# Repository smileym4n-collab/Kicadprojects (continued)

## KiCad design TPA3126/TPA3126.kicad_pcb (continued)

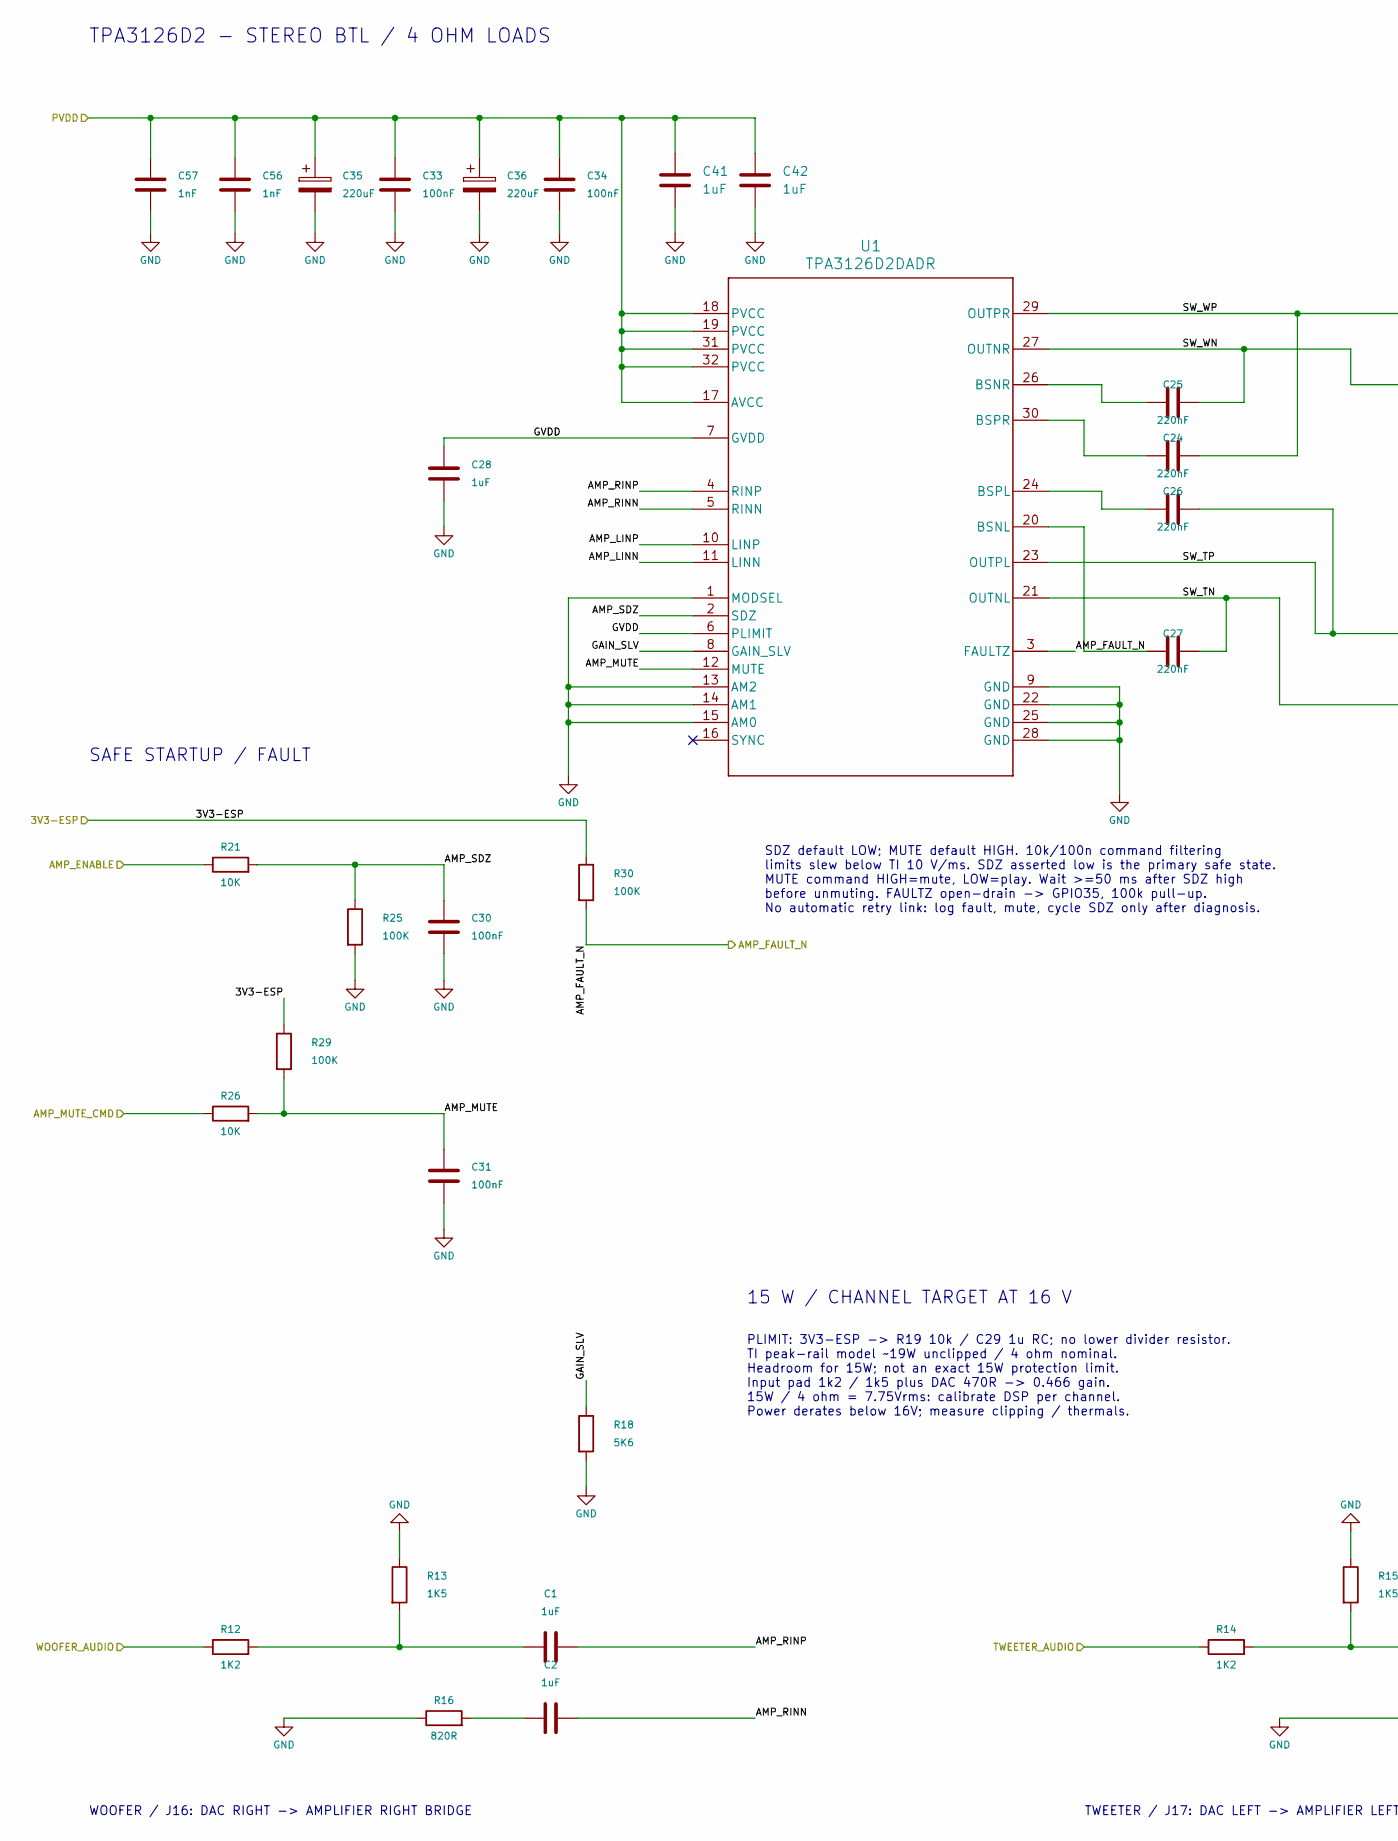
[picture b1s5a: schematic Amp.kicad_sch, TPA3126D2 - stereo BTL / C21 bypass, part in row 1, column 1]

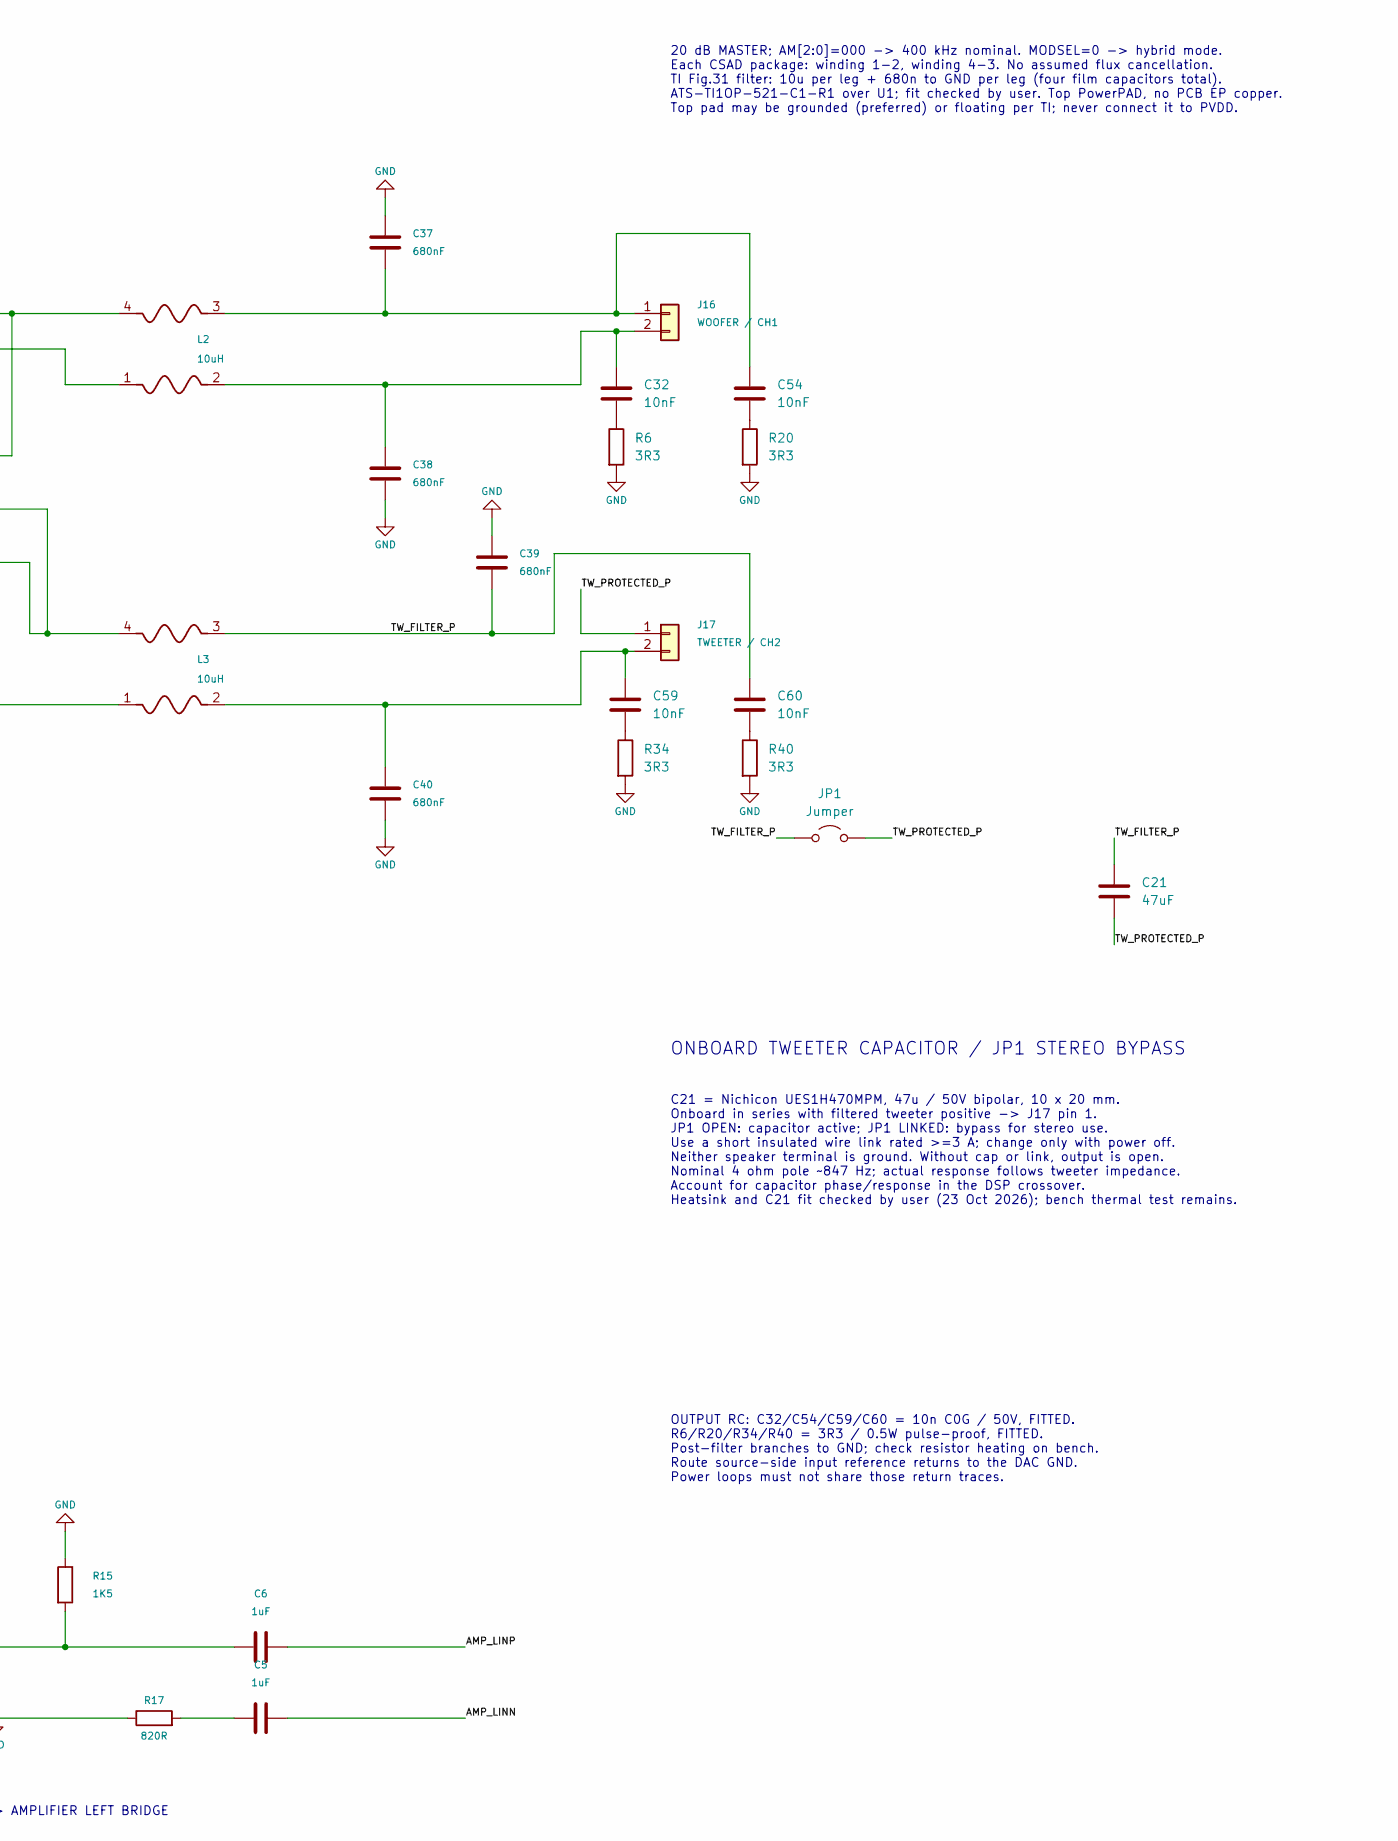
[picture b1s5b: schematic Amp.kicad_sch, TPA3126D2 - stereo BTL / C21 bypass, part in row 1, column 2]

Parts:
C1, C2, C5, C6: 1uF; C_Rect_L7.2mm_W5.0mm_P5.00mm; Voltage_Rating 63 V; Tolerance 5%; MPN R82DC4100AA60J
C21: 47uF; C_Radial_D10.0mm_H20.0mm_P5.00mm; Voltage_Rating 50 V; Tolerance 20%; MPN UES1H470MPM
C24, C25, C26, C27: 220nF; C_0805_2012Metric_Pad1.18x1.45mm_HandSolder; MPN CL21B224KAFNNNE
C28: 1uF; C_0805_2012Metric_Pad1.18x1.45mm_HandSolder; Voltage_Rating 25 V; Tolerance 10%; MPN C0805C105K3RACTU
C30, C31, C33, C34: 100nF; C_0603_1608Metric_Pad1.08x0.95mm_HandSolder; Voltage_Rating 50 V; Tolerance 10%; MPN MC0603B104K500CT
C32, C54, C59, C60: 10nF; C_0805_2012Metric_Pad1.18x1.45mm_HandSolder; Voltage_Rating 50 V; Tolerance 1%; MPN MC0805N103F500CT
C35, C36: 220uF; CP_Radial_D8.0mm_P3.50mm; MPN 35ZLH220MEFC8X11.5
C37, C38, C39, C40: 680nF; C_Rect_L18.0mm_W7.0mm_P15.00mm_FKS3_FKP3; MPN ECW-FE2W684J
C41, C42: 1uF; C_1206_3216Metric_Pad1.33x1.80mm_HandSolder; Manufacturer_Part_Number MCMHR50V105M4X7
C56, C57: 1nF; C_0603_1608Metric_Pad1.08x0.95mm_HandSolder; Voltage_Rating 50 V; Tolerance 10%; MPN CL10B102KB8NNNC
J16: WOOFER / CH1; Molex_KK-396_5273-02A_1x02_P3.96mm_Vertical; MPN 09-65-2028
J17: TWEETER / CH2; Molex_KK-396_5273-02A_1x02_P3.96mm_Vertical; MPN 09-65-2028
JP1: Jumper; TestPoint_2Pads_Pitch5.08mm_Drill1.3mm
L2, L3: 10uH; CSAD0660-100M; MPN CSAD0660-100M
R6, R20, R34, R40: 3R3; R_0805_2012Metric_Pad1.20x1.40mm_HandSolder; Tolerance 1%; MPN CRCW08053R30FKEAHP
R12, R14: 1K2; R_0805_2012Metric_Pad1.20x1.40mm_HandSolder; MPN RMCF0805FT1K20
R13, R15: 1K5; R_0805_2012Metric_Pad1.20x1.40mm_HandSolder; MPN RMCF0805FT1K50
R16, R17: 820R; R_0805_2012Metric_Pad1.20x1.40mm_HandSolder; Manufacturer_Part_Number RR1220P-821-D
R18: 5K6; R_0805_2012Metric_Pad1.20x1.40mm_HandSolder; MPN RMCF0805FT5K60
R21, R26: 10K; R_0805_2012Metric_Pad1.20x1.40mm_HandSolder; MPN RK73B2ATTD103J
R25, R29, R30: 100K; R_0805_2012Metric_Pad1.20x1.40mm_HandSolder; Manufacturer_Part_Number RK73B2ATTE104J
U1: TPA3126D2DADR; Texas_DAD0032A_HTSSOP-32_6.1x11mm_P0.65mm_TopEP3.71x3.81mm; MPN TPA3126D2DADR

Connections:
/3V3-ESP: R29.1, R30.1; also elsewhere on the board
/AMP/AMP_ENABLE: R21.1; also elsewhere on the board
/AMP/AMP_FAULT_N: R30.2, U1.3 (FAULTZ); also elsewhere on the board
/AMP/AMP_LINN: C5.2, U1.11 (LINN)
/AMP/AMP_LINP: C6.2, U1.10 (LINP)
/AMP/AMP_MUTE: C31.1, R26.2, R29.2, U1.12 (MUTE)
/AMP/AMP_MUTE_CMD: R26.1; also elsewhere on the board
/AMP/AMP_RINN: C2.2, U1.5 (RINN)
/AMP/AMP_RINP: C1.2, U1.4 (RINP)
/AMP/AMP_SDZ: C30.1, R21.2, R25.1, U1.2 (SDZ)
/AMP/GAIN_SLV: R18.1, U1.8 (GAIN_SLV)
/AMP/GVDD: C28.1, U1.6 (PLIMIT), U1.7 (GVDD)
/AMP/SW_TN: C27.2, L3.1, U1.21 (OUTNL)
/AMP/SW_TP: C26.2, L3.4, U1.23 (OUTPL)
/AMP/SW_WN: C25.2, L2.1, U1.27 (OUTNR)
/AMP/SW_WP: C24.2, L2.4, U1.29 (OUTPR)
/AMP/TWEETER_AUDIO: R14.1; also elsewhere on the board
/AMP/TW_FILTER_P: C21.1, C39.2, C60.1, JP1.1 (A), L3.3
/AMP/TW_PROTECTED_P: C21.2, J17.1, JP1.2 (B)
/AMP/WOOFER_AUDIO: R12.1; also elsewhere on the board
/PVDD: C33.1, C34.1, C35.1, C36.1, C41.1, C42.1, C56.1, C57.1, U1.17 (AVCC), U1.18 (PVCC), U1.19 (PVCC), U1.31 (PVCC), U1.32 (PVCC); also elsewhere on the board
GND: C28.2, C30.2, C31.2, C33.2, C34.2, C35.2, C36.2, C37.1, C38.2, C39.1, C40.2, C41.2, C42.2, C56.2, C57.2, R6.2, R13.1, R15.1, R16.1, R17.1, R18.2, R20.2, R25.2, R34.2, R40.2, U1.1 (MODSEL), U1.9 (GND), U1.13 (AM2), U1.14 (AM1), U1.15 (AM0), U1.22 (GND), U1.25 (GND), U1.28 (GND); also elsewhere on the board
unnamed: C1.1, R12.2, R13.2
unnamed: C2.1, R16.2
unnamed: C5.1, R17.2
unnamed: C6.1, R14.2, R15.2
unnamed: C32.2, R6.1
unnamed: C54.2, R20.1
unnamed: C59.2, R34.1
unnamed: C60.2, R40.1
unnamed: C37.2, C54.1, J16.1, L2.3
unnamed: C32.1, C38.1, J16.2, L2.2
unnamed: C40.1, C59.1, J17.2, L3.2
unnamed: C27.1, U1.20 (BSNL)
unnamed: C25.1, U1.26 (BSNR)
unnamed: C26.1, U1.24 (BSPL)
unnamed: C24.1, U1.30 (BSPR)

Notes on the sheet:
C21 = Nichicon UES1H470MPM, 47u / 50V bipolar, 10 x 20 mm. Onboard in series with filtered tweeter positive -> J17 pin 1. JP1 OPEN: capacitor active; JP1 LINKED: bypass for stereo use. Use a short insulated wire link rated >=3 A; change only with power off. Neither speaker terminal is ground. Witho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
ONBOARD TWEETER CAPACITOR / JP1 STEREO BYPASS
SAFE STARTUP / FAULT
WOOFER / J16: DAC RIGHT -> AMPLIFIER RIGHT BRIDGE
OUTPUT RC: C32/C54/C59/C60 = 10n C0G / 50V, FITTED. R6/R20/R34/R40 = 3R3 / 0.5W pulse-proof, FITTED. Post-filter branches to GND; check resistor heating on bench. Route source-side input reference returns to the DAC GND. Power loops must not share those return traces.
SDZ default LOW; MUTE default HIGH. 10k/100n command filtering limits slew below TI 10 V/ms. SDZ asserted low is the primary safe state. MUTE command HIGH=mute, LOW=play. Wait >=50 ms after SDZ high before unmuting. FAULTZ open-drain -> GPIO35, 100k pull-up. No automatic retry link: log fault, mute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
TPA3126D2 - STEREO BTL / 4 OHM LOADS
15 W / CHANNEL TARGET AT 16 V
TWEETER / J17: DAC LEFT -> AMPLIFIER LEFT BRIDGE
20 dB MASTER; AM[2:0]=000 -> 400 kHz nominal. MODSEL=0 -> hybrid mode. Each CSAD package: winding 1-2, winding 4-3. No assumed flux cancellation. TI Fig.31 filter: 10u per leg + 680n to GND per leg (four film capacitors total). ATS-TI1OP-521-C1-R1 over U1; fit checked by user. Top PowerPAD, no PCB 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
PLIMIT: 3V3-ESP -> R19 10k / C29 1u RC; no lower divider resistor. TI peak-rail model ~19W unclipped / 4 ohm nominal. Headroom for 15W; not an exact 15W protection limit. Input pad 1k2 / 1k5 plus DAC 470R -> 0.466 gain. 15W / 4 ohm = 7.75Vrms: calibrate DSP per channel. Power derates below 16V; mea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

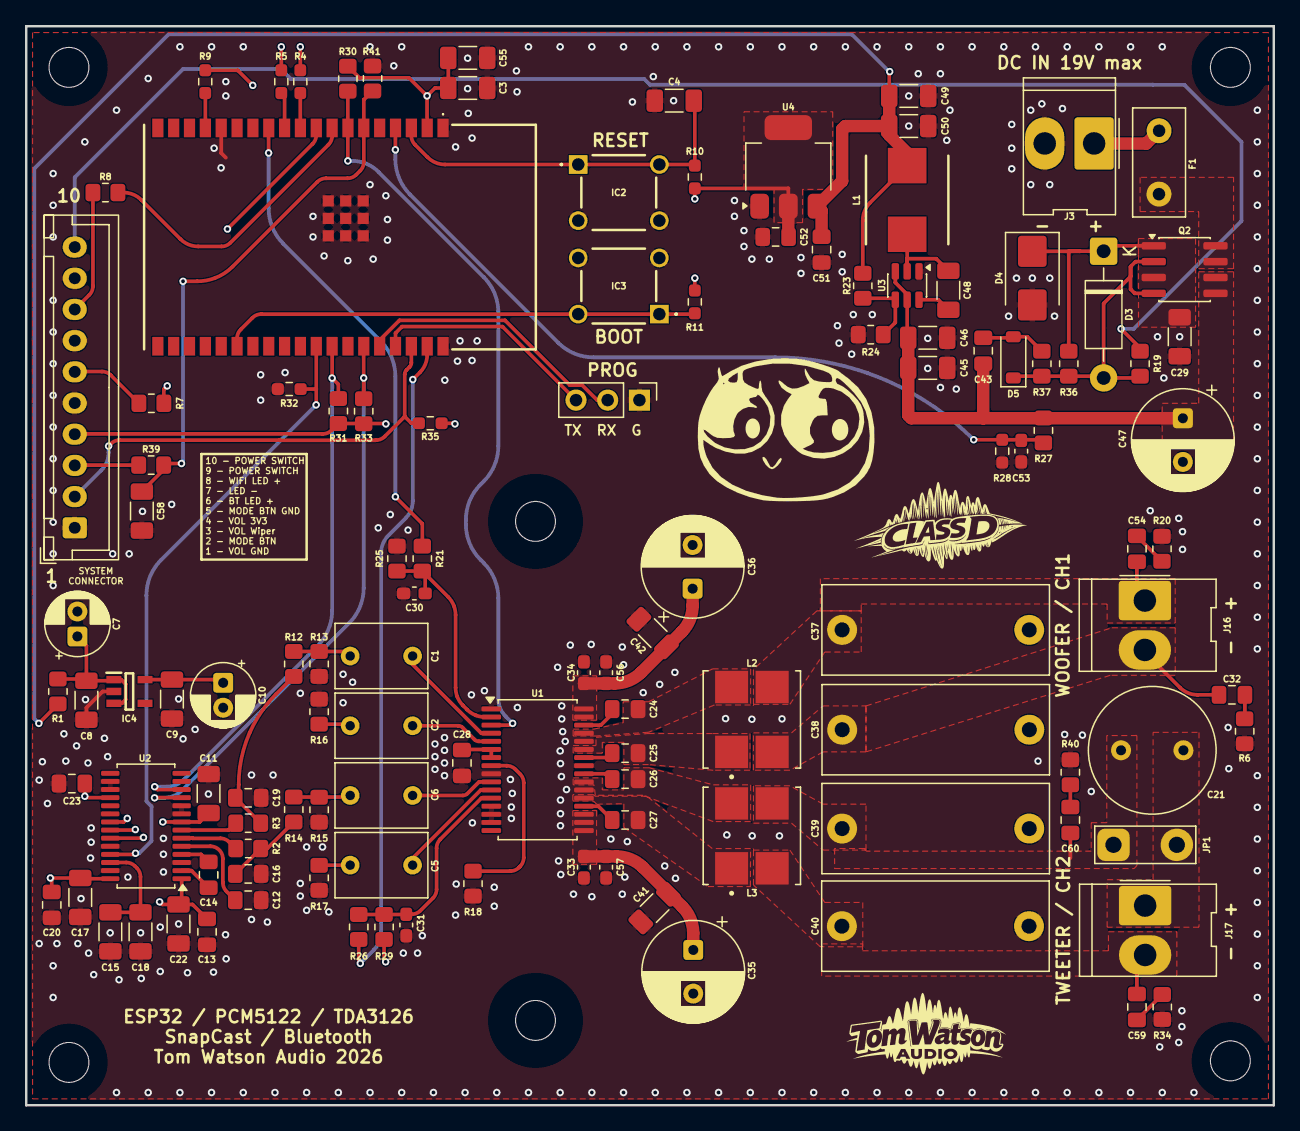
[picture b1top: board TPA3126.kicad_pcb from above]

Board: 4 copper layers, 100.0 x 86.5 mm, 125 parts (0 on the bottom side), 76 nets.

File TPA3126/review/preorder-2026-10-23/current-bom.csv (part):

Reference,Value,Footprint,Recorded MPN,Inventory ID,Saved assembly note,Review status
H1,MountingHole,MountingHole:MountingHole_3.2mm_M3,,,,Saved fields only; not a purchase approval
H2,MountingHole,MountingHole:MountingHole_3.2mm_M3,,,,Saved fields only; not a purchase approval
H3,MountingHole,MountingHole:MountingHole_3.2mm_M3,,,,Saved fields only; not a purchase approval
H4,MountingHole,MountingHole:MountingHole_3.2mm_M3,,,,Saved fields only; not a purchase approval
HS1,Heatsink,Custom:Heatsink_ATS_ATS-TI1OP-521-C1-R1_50x13.9mm_H25mm_P40mm,,,,Saved fields only; not a purchase approval
C3,100nF,Capacitor_SMD:C_1206_3216Metric_Pad1.33x1.80mm_HandSolder,C1206C104K5RACTU,157,,Saved fields only; not a purchase approval
C4,1uF,Capacitor_SMD:C_1206_3216Metric_Pad1.33x1.80mm_HandSolder,CL31B105KBHNFNE,181,,Saved fields only; not a purchase approval
C55,22uF,Capacitor_SMD:C_1206_3216Metric_Pad1.33x1.80mm_HandSolder,CL31A226KAHNNNE,202,,Saved fields only; not a purchase approval
C58,100nF,Capacitor_SMD:C_1206_3216Metric_Pad1.33x1.80mm_HandSolder,C1206C104K5RACTU,157,"3216 metric X7R; place beside GPIO34, short GND return.",Saved fields only; not a purchase approval
IC2,RESET,Custom:TS026650BK100SCRD,TS02-66-50-BK-100-SCR-D,537,,Saved fields only; not a purchase approval
IC3,BOOT,Custom:TS026650BK100SCRD,TS02-66-50-BK-100-SCR-D,537,,Saved fields only; not a purchase approval
IC5,ESP32-Wrover-IE-N16R8,Custom:ESP32-WROVER-IE-N16R8,ESP32-WROVER-IE-N16R8,96,,Saved fields only; not a purchase approval
J2,SYSTEM CONNECTOR,Connector_JST:JST_XH_B8B-XH-A_1x08_P2.50mm_Vertical,,,,Saved fields only; not a purchase approval
J3,PROG,Connector_PinHeader_2.54mm:PinHeader_1x04_P2.54mm_Vertical,,,,Saved fields only; not a purchase approval
R4,22R,Resistor_SMD:R_0603_1608Metric_Pad0.98x0.95mm_HandSolder,RK73B1JTTD220J,185,"22R damping resistors, 1608, 5%.",Saved fields only; not a purchase approval
R5,22R,Resistor_SMD:R_0603_1608Metric_Pad0.98x0.95mm_HandSolder,RK73B1JTTD220J,185,"22R damping resistors, 1608, 5%.",Saved fields only; not a purchase approval
R7,1K,Resistor_SMD:R_0805_2012Metric_Pad1.20x1.40mm_HandSolder,,223,"1k utility resistors, 2012, 5%; no exact manufacturer MPN recorded.",Saved fields only; not a purchase approval
R8,1K,Resistor_SMD:R_0805_2012Metric_Pad1.20x1.40mm_HandSolder,,223,"1k utility resistors, 2012, 5%; no exact manufacturer MPN recorded.",Saved fields only; not a purchase approval
R9,22R,Resistor_SMD:R_0603_1608Metric_Pad0.98x0.95mm_HandSolder,RK73B1JTTD220J,185,"22R damping resistors, 1608, 5%.",Saved fields only; not a purchase approval
R10,10K,Resistor_SMD:R_0603_1608Metric_Pad0.98x0.95mm_HandSolder,,231,"10k, 1608, 1%; no exact manufacturer MPN recorded.",Saved fields only; not a purchase approval
R11,10K,Resistor_SMD:R_0603_1608Metric_Pad0.98x0.95mm_HandSolder,,231,"10k, 1608, 1%; no exact manufacturer MPN recorded.",Saved fields only; not a purchase approval
R31,4K7,Resistor_SMD:R_0805_2012Metric_Pad1.20x1.40mm_HandSolder,RMCF0805FT4K70,493,,Saved fields only; not a purchase approval
R33,4K7,Resistor_SMD:R_0805_2012Metric_Pad1.20x1.40mm_HandSolder,RMCF0805FT4K70,493,,Saved fields only; not a purchase approval
R35,10K,Resistor_SMD:R_0603_1608Metric_Pad0.98x0.95mm_HandSolder,,231,"10k, 1608, 1%; no exact manufacturer MPN recorded.",Saved fields only; not a purchase approval
R39,10K,Resistor_SMD:R_0805_2012Metric_Pad1.20x1.40mm_HandSolder,RK73B2ATTD103J,194,"2012 metric, 5%; volume ADC divider/filter series resistor.",Saved fields only; not a purchase approval
R41,22K,Resistor_SMD:R_0805_2012Metric_Pad1.20x1.40mm_HandSolder,RR1220P-223-D,511,"22k, 0.5%, 2012 metric. ADC divider shunt and open-wiper pull-down. Owned inventory ID511.",Saved fields only; not a purchase approval
C7,10uF,Capacitor_THT:CP_Radial_D5.0mm_P2.00mm,UFW1H100MDD,426,,Saved fields only; not a purchase approval
C8,1uF,Capacitor_SMD:C_1206_3216Metric_Pad1.33x1.80mm_HandSolder,CL31B105KBHNFNE,181,,Saved fields only; not a purchase approval
C9,1uF,Capacitor_SMD:C_1206_3216Metric_Pad1.33x1.80mm_HandSolder,CL31B105KBHNFNE,181,,Saved fields only; not a purchase approval
C10,22uF,Capacitor_THT:CP_Radial_D5.0mm_P2.00mm,UFW1E220MDD,442,,Saved fields only; not a purchase approval
C11,100nF,Capacitor_SMD:C_1206_3216Metric_Pad1.33x1.80mm_HandSolder,C1206C104K5RACTU,157,,Saved fields only; not a purchase approval
C12,2.2uF,Capacitor_SMD:C_0805_2012Metric_Pad1.18x1.45mm_HandSolder,CL21B225KPFNNNE,182,Charge pump MLCC; verify effective capacitance and ripple on bench.,Saved fields only; not a purchase approval
C13,10uF,Capacitor_SMD:C_0805_2012Metric_Pad1.18x1.45mm_HandSolder,CL21A106KOQNNNF,184,,Saved fields only; not a purchase approval
C14,2.2uF,Capacitor_SMD:C_0805_2012Metric_Pad1.18x1.45mm_HandSolder,CL21B225KPFNNNE,182,Charge pump MLCC; verify effective capacitance and ripple on bench.,Saved fields only; not a purchase approval
C15,100nF,Capacitor_SMD:C_1206_3216Metric_Pad1.33x1.80mm_HandSolder,C1206C104K5RACTU,157,,Saved fields only; not a purchase approval
C16,2.7nF,Capacitor_SMD:C_0805_2012Metric_Pad1.18x1.45mm_HandSolder,0805N272J500CT,161,,Saved fields only; not a purchase approval
C17,100nF,Capacitor_SMD:C_1206_3216Metric_Pad1.33x1.80mm_HandSolder,C1206C104K5RACTU,157,,Saved fields only; not a purchase approval
C18,10uF,Capacitor_SMD:C_1206_3216Metric_Pad1.33x1.80mm_HandSolder,TMK316B7106KL-TD,135,,Saved fields only; not a purchase approval
C19,2.7nF,Capacitor_SMD:C_0805_2012Metric_Pad1.18x1.45mm_HandSolder,0805N272J500CT,161,,Saved fields only; not a purchase approval
C20,10uF,Capacitor_SMD:C_0805_2012Metric_Pad1.18x1.45mm_HandSolder,CL21A106KOQNNNF,184,,Saved fields only; not a purchase approval
C22,100nF,Capacitor_SMD:C_1206_3216Metric_Pad1.33x1.80mm_HandSolder,C1206C104K5RACTU,157,,Saved fields only; not a purchase approval
C23,10uF,Capacitor_SMD:C_0805_2012Metric_Pad1.18x1.45mm_HandSolder,CL21A106KOQNNNF,184,,Saved fields only; not a purchase approval
IC4,TPS7A2033,Custom:SOT95P280X145-5N,TPS7A2033PDBVR,28,,Saved fields only; not a purchase approval
R1,2R2,Resistor_SMD:R_0805_2012Metric_Pad1.20x1.40mm_HandSolder,,335,"Multicomp Pro 2R2, 1%, 2012; exact MPN not recorded.",Saved fields only; not a purchase approval
R2,470R,Resistor_SMD:R_0805_2012Metric_Pad1.20x1.40mm_HandSolder,,218,"470R, 2012; exact manufacturer/tolerance not recorded. Confirm <=5%.",Saved fields only; not a purchase approval
R3,470R,Resistor_SMD:R_0805_2012Metric_Pad1.20x1.40mm_HandSolder,,218,"470R, 2012; exact manufacturer/tolerance not recorded. Confirm <=5%.",Saved fields only; not a purchase approval
R32,10k,Resistor_SMD:R_0603_1608Metric_Pad0.98x0.95mm_HandSolder,RC0603FR-0710KL,231,"10k, 1608, 1%; no exact manufacturer MPN recorded.",Saved fields only; not a purchase approval
U2,PCM5122PW,Package_SO:TSSOP-28_4.4x9.7mm_P0.65mm,PCM5122PWR,491,MCP explicitly reports zero. Existing circuit does not establish ownership.,Saved fields only; not a purchase approval
C1,1uF,Capacitor_THT:C_Rect_L7.2mm_W5.0mm_P5.00mm,MKS2C041001F00JSSD,132,"Stock is Kemet generic 1u / 63 V, body noted 7x5 mm. Check 5 mm pitch; WIMA MPN is a verified purchase fallback, not a claim about stock identity.",Saved fields only; not a purchase approval
C2,1uF,Capacitor_THT:C_Rect_L7.2mm_W5.0mm_P5.00mm,MKS2C041001F00JSSD,132,"Stock is Kemet generic 1u / 63 V, body noted 7x5 mm. Check 5 mm pitch; WIMA MPN is a verified purchase fallback, not a claim about stock identity.",Saved fields only; not a purchase approval
C5,1uF,Capacitor_THT:C_Rect_L7.2mm_W5.0mm_P5.00mm,MKS2C041001F00JSSD,132,"Stock is Kemet generic 1u / 63 V, body noted 7x5 mm. Check 5 mm pitch; WIMA MPN is a verified purchase fallback, not a claim about stock identity.",Saved fields only; not a purchase approval
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
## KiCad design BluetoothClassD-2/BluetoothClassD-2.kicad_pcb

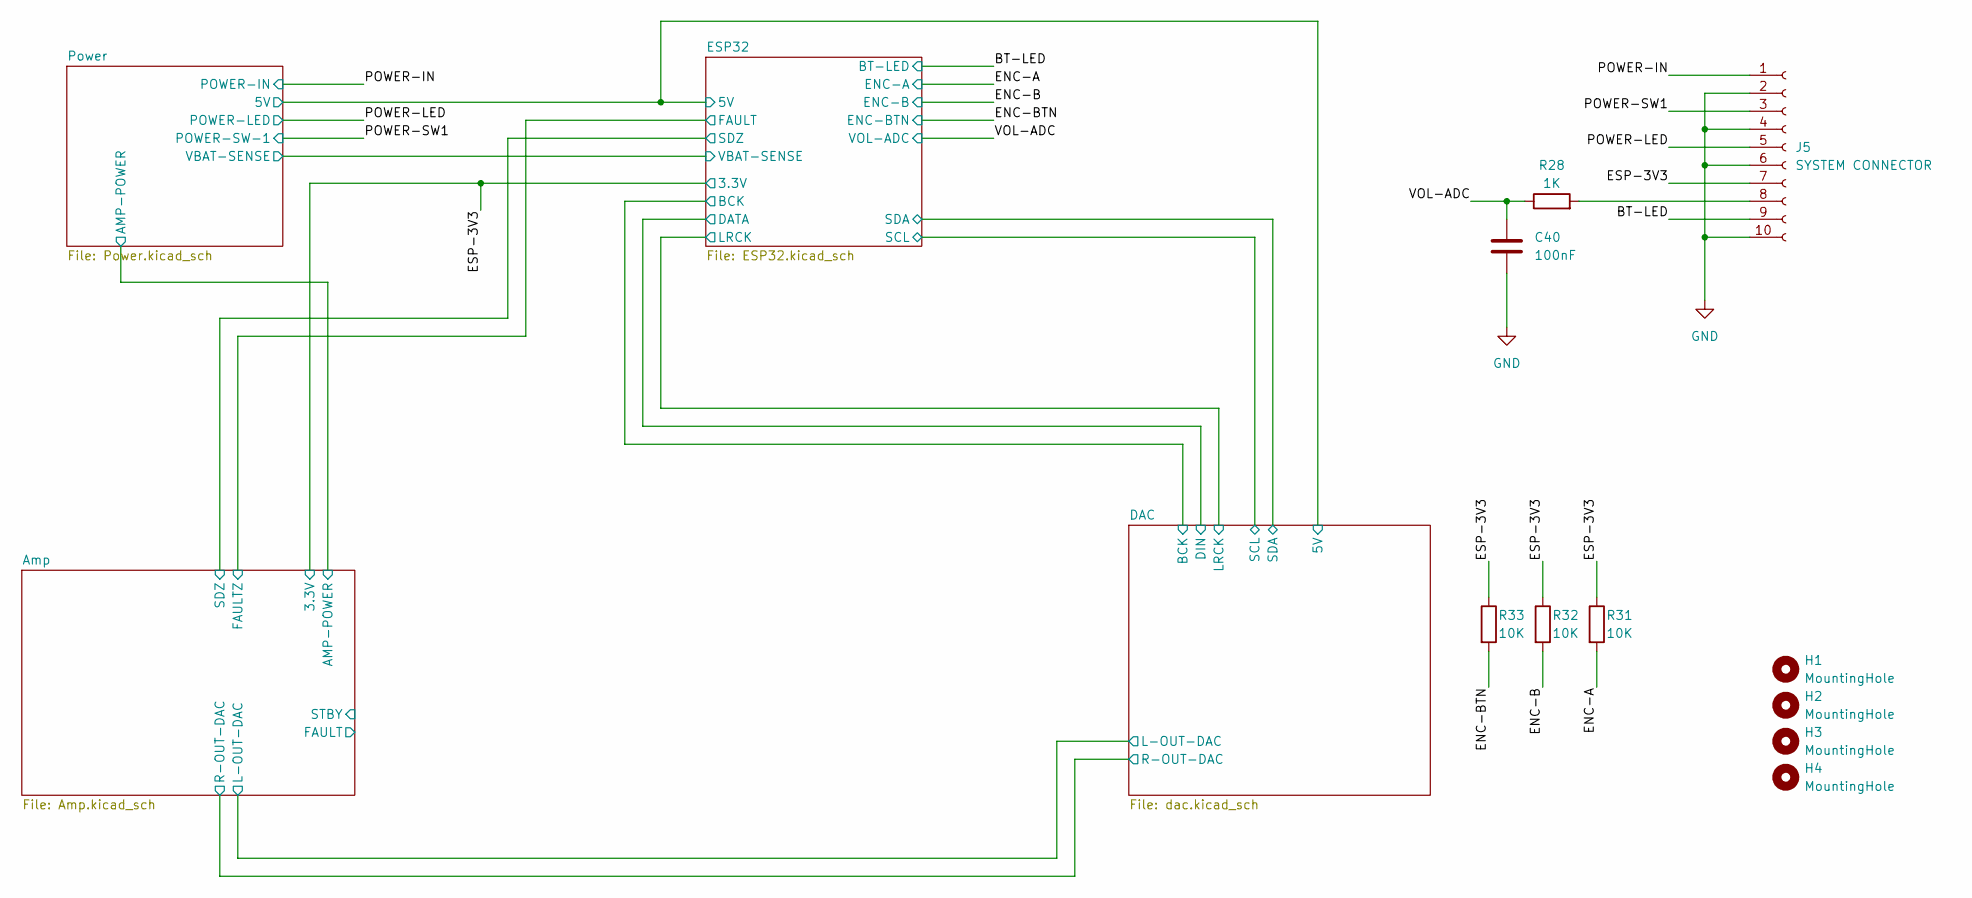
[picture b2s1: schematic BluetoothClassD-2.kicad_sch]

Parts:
C40: 100nF; C_0603_1608Metric_Pad1.08x0.95mm_HandSolder
H1, H2, H3, H4: MountingHole; MountingHole_3.2mm_M3
J5: SYSTEM CONNECTOR; JST_XH_B10B-XH-A_1x10_P2.50mm_Vertical
R28: 1K; R_0805_2012Metric_Pad1.20x1.40mm_HandSolder
R31, R32, R33: 10K; R_0603_1608Metric_Pad0.98x0.95mm_HandSolder

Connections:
/BT-LED: J5.9; also elsewhere on the board
/ENC-A: R31.2
/ENC-B: R32.2
/ENC-BTN: R33.2; also elsewhere on the board
/ESP-3V3: J5.7, R31.1, R32.1, R33.1; also elsewhere on the board
/POWER-IN: J5.1; also elsewhere on the board
/POWER-LED: J5.5; also elsewhere on the board
/POWER-SW1: J5.3; also elsewhere on the board
/VOL-ADC: C40.1, R28.1; also elsewhere on the board
GND: C40.2, J5.2, J5.4, J5.6, J5.10; also elsewhere on the board
unnamed: J5.8, R28.2

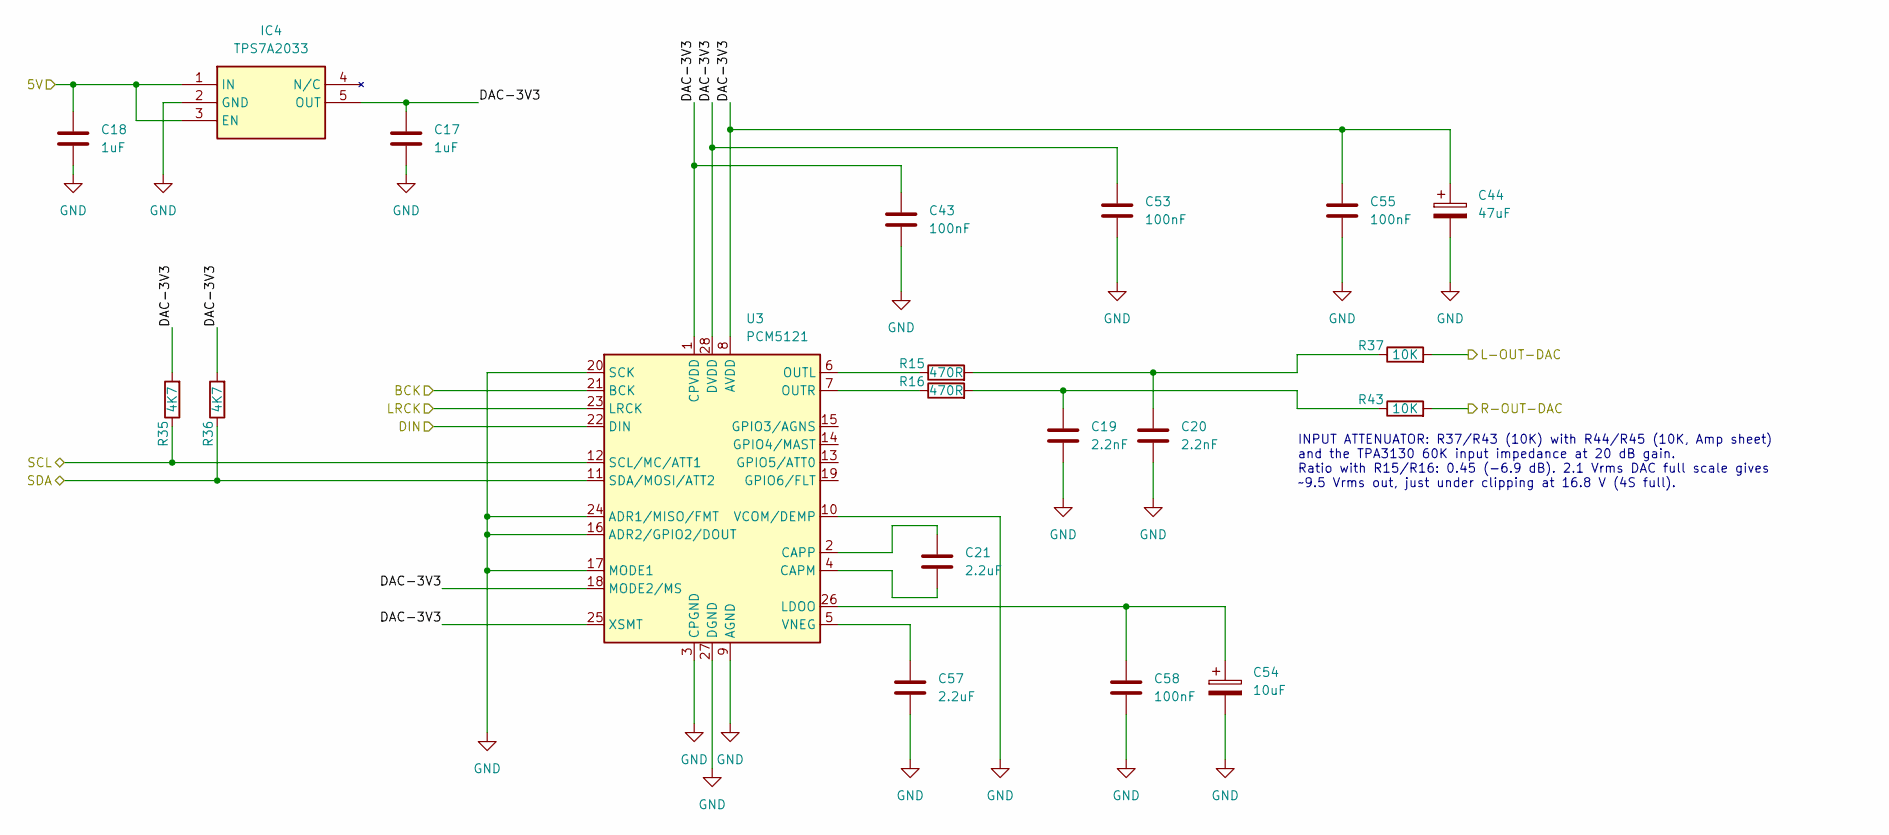
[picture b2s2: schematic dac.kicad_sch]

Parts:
C17, C18: 1uF; C_0805_2012Metric_Pad1.18x1.45mm_HandSolder
C19, C20: 2.2nF; C_0805_2012Metric_Pad1.18x1.45mm_HandSolder
C21, C57: 2.2uF; C_0805_2012Metric_Pad1.18x1.45mm_HandSolder
C43, C53, C55, C58: 100nF; C_0603_1608Metric_Pad1.08x0.95mm_HandSolder
C44: 47uF; CP_Radial_D6.3mm_P2.50mm
C54: 10uF; CP_Radial_D4.0mm_P2.00mm
IC4: TPS7A2033; SOT95P280X145-5N; Mouser Part Number 595-TPS7A2033PDBVR
R15, R16: 470R; R_0805_2012Metric_Pad1.20x1.40mm_HandSolder
R35, R36: 4K7; R_0805_2012Metric_Pad1.20x1.40mm_HandSolder
R37, R43: 10K; R_0805_2012Metric_Pad1.20x1.40mm_HandSolder; Manufacturer_Part_Number RR1220P-103-D
U3: PCM5121; TSSOP-28_4.4x9.7mm_P0.65mm

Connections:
/Amp/L-OUT-DAC: R37.2; also elsewhere on the board
/Amp/R-OUT-DAC: R43.2; also elsewhere on the board
/DAC/5V: C18.1, IC4.1 (IN), IC4.3 (EN); also elsewhere on the board
/DAC/BCK: U3.21 (BCK); also elsewhere on the board
/DAC/DAC-3V3: C17.1, C43.1, C44.1, C53.1, C55.1, IC4.5 (OUT), R35.2, R36.2, U3.1 (CPVDD), U3.8 (AVDD), U3.18 (MODE2/MS), U3.25 (XSMT), U3.28 (DVDD)
/DAC/DIN: U3.22 (DIN); also elsewhere on the board
/DAC/LRCK: U3.23 (LRCK); also elsewhere on the board
/DAC/SCL: R35.1, U3.12 (SCL/MC/ATT1); also elsewhere on the board
/DAC/SDA: R36.1, U3.11 (SDA/MOSI/ATT2); also elsewhere on the board
GND: C17.2, C18.2, C19.2, C20.2, C43.2, C44.2, C53.2, C54.2, C55.2, C57.2, C58.2, IC4.2 (GND), U3.3 (CPGND), U3.9 (AGND), U3.10 (VCOM/DEMP), U3.16 (ADR2/GPIO2/DOUT), U3.17 (MODE1), U3.20 (SCK), U3.24 (ADR1/MISO/FMT), U3.27 (DGND); also elsewhere on the board
unnamed: C19.1, R16.2, R43.1
unnamed: C20.1, R15.2, R37.1
unnamed: C21.2, U3.4 (CAPM)
unnamed: C21.1, U3.2 (CAPP)
unnamed: C54.1, C58.1, U3.26 (LDOO)
unnamed: R15.1, U3.6 (OUTL)
unnamed: R16.1, U3.7 (OUTR)
unnamed: C57.1, U3.5 (VNEG)

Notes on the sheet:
INPUT ATTENUATOR: R37/R43 (10K) with R44/R45 (10K, Amp sheet) and the TPA3130 60K input impedance at 20 dB gain. Ratio with R15/R16: 0.45 (-6.9 dB). 2.1 Vrms DAC full scale gives ~9.5 Vrms out, just under clipping at 16.8 V (4S full).

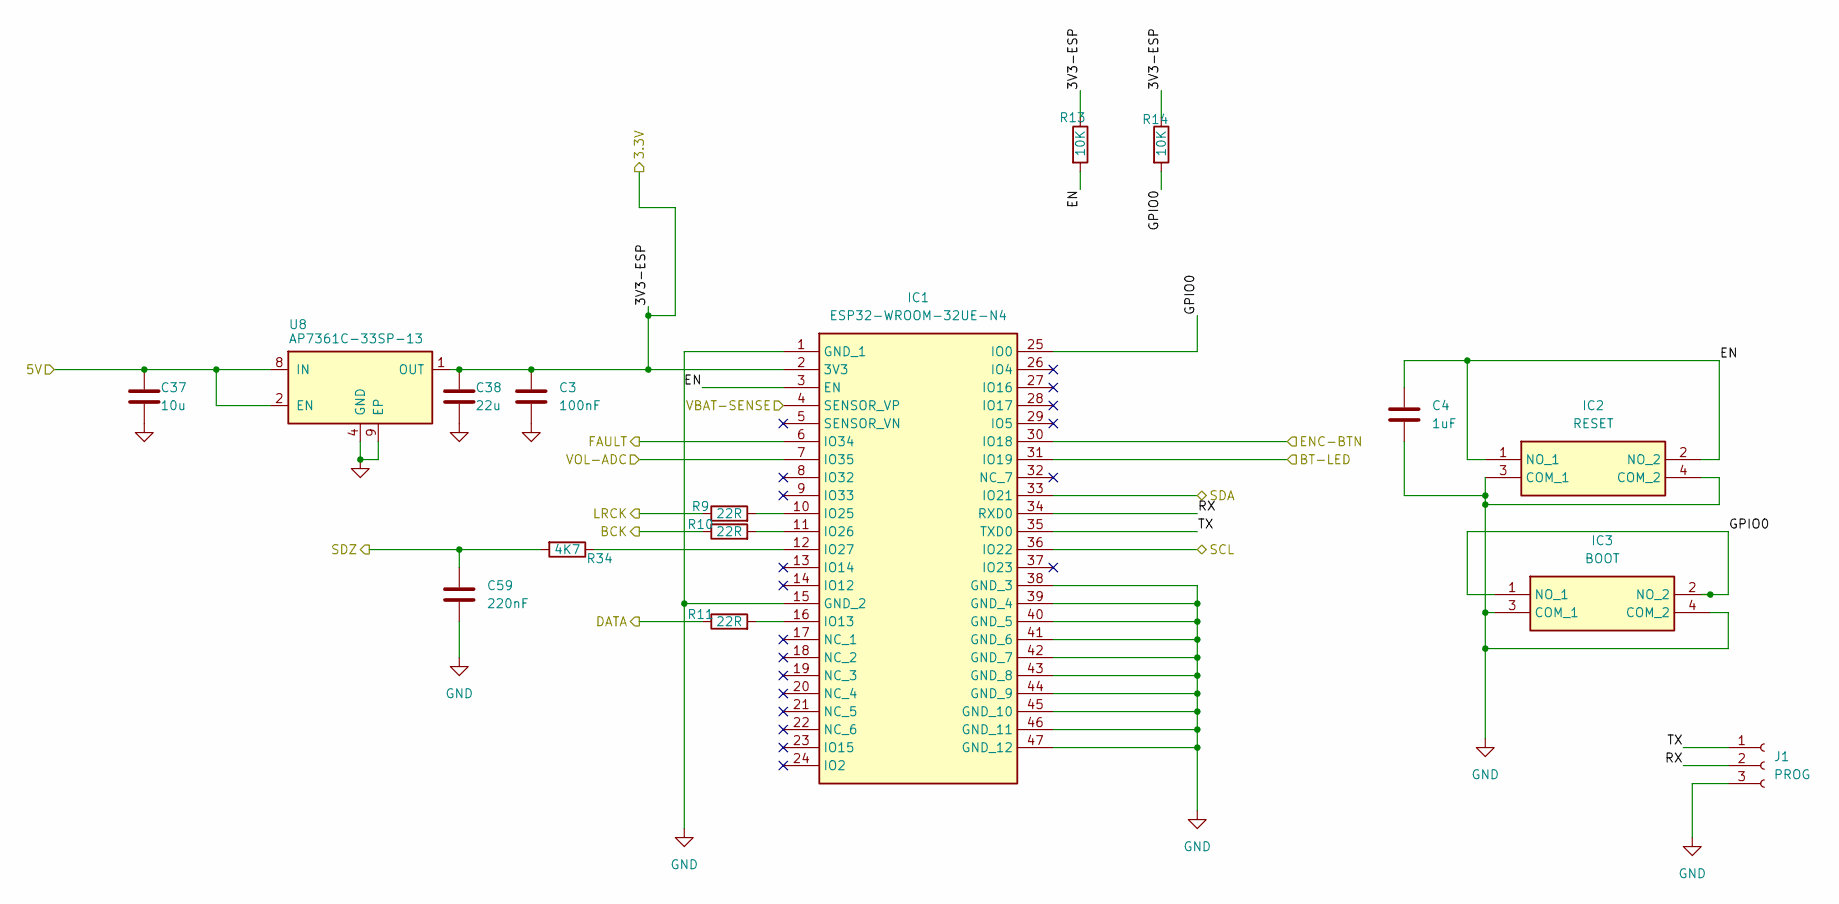
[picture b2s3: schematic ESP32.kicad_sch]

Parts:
C3: 100nF; C_0603_1608Metric_Pad1.08x0.95mm_HandSolder
C4: 1uF; C_1206_3216Metric_Pad1.33x1.80mm_HandSolder
C37: 10u; C_1206_3216Metric; MPN TMK316B7106KL-TD
C38: 22u; C_0805_2012Metric_Pad1.18x1.45mm_HandSolder; MPN EMK316BB7226ML-T
C59: 220nF; C_0805_2012Metric_Pad1.18x1.45mm_HandSolder
IC1: ESP32-WROOM-32UE-N4; ESP32WROOM32UEN8R2; Manufacturer_Part_Number ESP32-WROOM-32UE-N4
IC2: RESET; TS026650BK100SCRD; Mouser Part Number 179-TS026650BK100SCR
IC3: BOOT; TS026650BK100SCRD; Mouser Part Number 179-TS026650BK100SCR
J1: PROG; PinHeader_1x03_P2.54mm_Vertical
R9, R10, R11: 22R; R_0603_1608Metric_Pad0.98x0.95mm_HandSolder
R13, R14: 10K; R_0603_1608Metric_Pad0.98x0.95mm_HandSolder
R34: 4K7; R_0805_2012Metric_Pad1.20x1.40mm_HandSolder
U8: AP7361C-33SP-13; Diodes_SO-8EP; MPN AP7361C-33SP-13

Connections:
/Amp/FAULTZ: IC1.6 (IO34); also elsewhere on the board
/Amp/SDZ: C59.1, R34.2; also elsewhere on the board
/BT-LED: IC1.31 (IO19); also elsewhere on the board
/DAC/5V: C37.1, U8.2 (EN), U8.8 (IN); also elsewhere on the board
/DAC/BCK: R10.1; also elsewhere on the board
/DAC/DIN: R11.1; also elsewhere on the board
/DAC/LRCK: R9.1; also elsewhere on the board
/DAC/SCL: IC1.36 (IO22); also elsewhere on the board
/DAC/SDA: IC1.33 (IO21); also elsewhere on the board
/ENC-BTN: IC1.30 (IO18); also elsewhere on the board
/ESP32/EN: C4.1, IC1.3 (EN), IC2.1 (NO_1), IC2.2 (NO_2), R13.2
/ESP32/GPIO0: IC1.25 (IO0), IC3.1 (NO_1), IC3.2 (NO_2), R14.2
/ESP32/RX: IC1.34 (RXD0), J1.2
/ESP32/TX: IC1.35 (TXD0), J1.1
/ESP32/VBAT-SENSE: IC1.4 (SENSOR_VP); also elsewhere on the board
/ESP-3V3: C3.1, C38.1, IC1.2 (3V3), R13.1, R14.1, U8.1 (OUT); also elsewhere on the board
/VOL-ADC: IC1.7 (IO35); also elsewhere on the board
GND: C3.2, C4.2, C37.2, C38.2, C59.2, IC1.1 (GND_1), IC1.15 (GND_2), IC1.38 (GND_3), IC1.39 (GND_4), IC1.40 (GND_5), IC1.41 (GND_6), IC1.42 (GND_7), IC1.43 (GND_8), IC1.44 (GND_9), IC1.45 (GND_10), IC1.46 (GND_11), IC1.47 (GND_12), IC2.3 (COM_1), IC2.4 (COM_2), IC3.3 (COM_1), IC3.4 (COM_2), J1.3, U8.4 (GND), U8.9 (EP); also elsewhere on the board
unnamed: IC1.16 (IO13), R11.2
unnamed: IC1.10 (IO25), R9.2
unnamed: IC1.11 (IO26), R10.2
unnamed: IC1.12 (IO27), R34.1
